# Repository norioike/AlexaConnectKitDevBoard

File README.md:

# AlexaConnectKit Dev-Boardについて
この基板は主にAlexa Connect Kitを使ったデバイスを開発するための開発ボードとして作りました。
RP2040をMCUにAlexaConnectKitのモジュール "ESP32-PICO-V3-ZERO"と通信ができるようになっています。
またRP2040のGPIOは出せるだけ出しているので、センサー類を追加したり駆動系を追加する事でオリジナルのAlexa対応ロボットなどが作れるようになる（と思います)

ただ、この基板単体でも遊べるようにタクトスイッチとフルカラーLEDを実装しています。
しかし、私のミスでフルカラーLEDは点灯しません。電源は5Vにもかかわらず、3.3Vを供給。そのため命令を送っても点灯しません。

部品が余ったので数個だけ頒布しています。
もしよろしければこちらをご覧下さい。

https://www.switch-science.com/catalog/8078/

## Alexa Connect Kitについて
ハードウェアにAlexaを簡単に統合できるようにするためのマネージメントサービスで、これを使うことでAlexaに話しかけるとハードウェアを動かしたり、
逆にセンサー情報をAlexaに送る事ができるハードウェアを簡単に開発する事ができるようになります。
具体的にAlexa内蔵の電子レンジみたいなものを作ることも可能です。

システムの構成は、従来ハードウェアにAlexaと通信ができるモジュールを搭載することで実現できるようになっています。こうすることで開発負荷を下げることを想定しているのだと思います。
今回はESP32-PICO-V3-ZEROがそのモジュールで、この中にAlexaと通信するために必要なファームウェアが書かれており、開発者がこのモジュールとUARTなどで通信できるようにハードウェアを開発すればOKです。
すべての制御は自身が実装したMCUに書くことになります。ここでAlexaに対して命令を送ったり、受け取ったりできるようにすることでAlexa対応のオリジナルデバイスが実現できます。

## セットアップについて
セットアップはWikiにまとめています。このセットアップが完了できれば、あとは自由に開発するだけの状態になります。

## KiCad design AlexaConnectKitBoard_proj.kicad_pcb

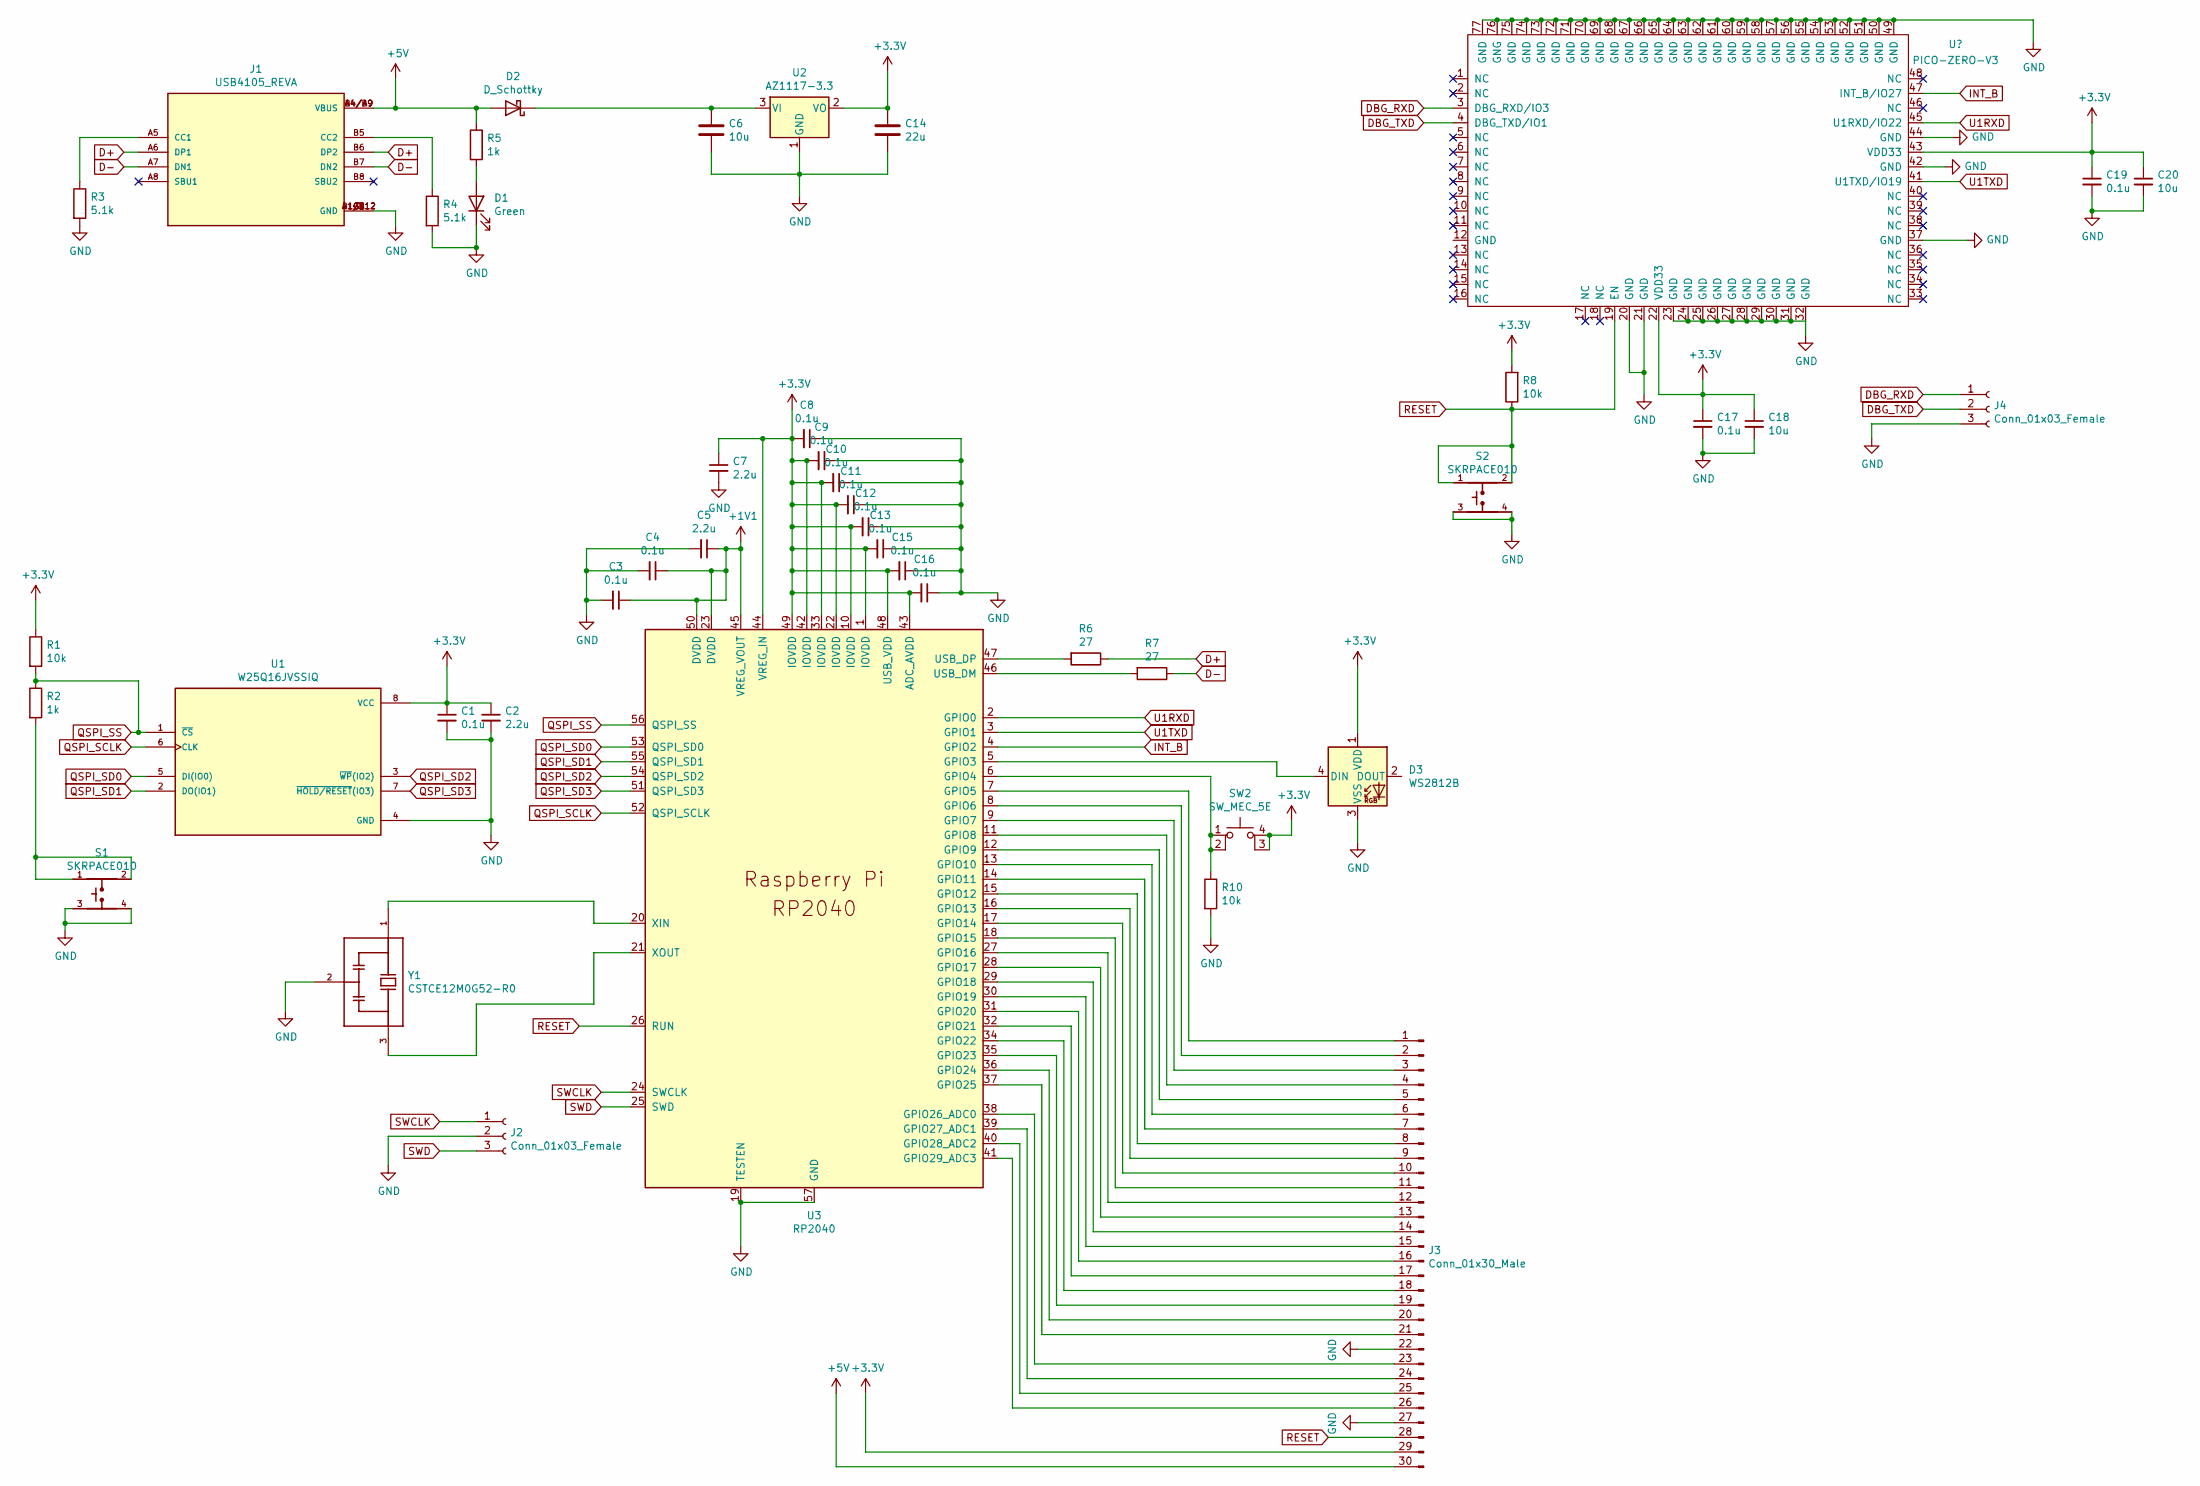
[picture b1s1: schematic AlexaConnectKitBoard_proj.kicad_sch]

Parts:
C1, C3, C4, C8, C9, C10, C11, C12, C13, C15, C16, C17, C19: 0.1u; C_0603_1608Metric
C2, C5, C7: 2.2u; C_0603_1608Metric
C6, C18, C20: 10u; C_0805_2012Metric
C14: 22u; C_0603_1608Metric
D1: Green; LED_0603_1608Metric_Pad1.05x0.95mm_HandSolder
D2: D_Schottky; D_SOD-123F
D3: WS2812B; LED_WS2812B_PLCC4_5.0x5.0mm_P3.2mm
J1: USB4105_REVA; GCT_USB4105_REVA; PARTREV 0.2
J2, J4: Conn_01x03_Female; PinHeader_1x03_P2.54mm_Vertical
J3: Conn_01x30_Male; PinHeader_1x30_P2.54mm_Vertical
R1, R8, R10: 10k; R_0603_1608Metric
R2: 1k; R_0603_1608Metric
R3, R4: 5.1k; R_0603_1608Metric_Pad0.98x0.95mm_HandSolder
R5: 1k; R_0603_1608Metric_Pad0.98x0.95mm_HandSolder
R6, R7: 27; R_0603_1608Metric
S1, S2: SKRPACE010; SW_SKRPACE010
SW2: SW_MEC_5E; SW_SPST_Omron_B3FS-105xP
U1: W25Q16JVSSIQ; SOIC127P790X216-8N
U2: AZ1117-3.3; SOT-223-3_TabPin2
U3: RP2040; RP2040-QFN-56
Y1: CSTCE12M0G52-R0; OSC_CSTCE12M0G52-R0; PARTREV May 7, 2019

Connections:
+1V1: C3.1, C4.1, C5.1, U3.23 (DVDD), U3.45 (VREG_VOUT), U3.50 (DVDD)
+3V3: C1.1, C2.1, C7.1, C8.2, C9.2, C10.2, C11.2, C12.2, C13.2, C14.1, C15.2, C16.2, C17.1, C18.1, C19.1, C20.1, D3.1 (VDD), J3.29, R1.1, R8.2, SW2.3 (K), SW2.4 (A), U1.8 (VCC), U2.2 (VO), U3.1 (IOVDD), U3.10 (IOVDD), U3.22 (IOVDD), U3.33 (IOVDD), U3.42 (IOVDD), U3.43 (ADC_AVDD), U3.44 (VREG_IN), U3.48 (USB_VDD), U3.49 (IOVDD); also elsewhere on the board
+5V: D2.2 (A), J1.A4/B9 (VBUS), J1.B4/A9 (VBUS), J3.30, R5.1
D+: J1.A6 (DP1), J1.B6 (DP2), R6.1
D-: J1.A7 (DN1), J1.B7 (DN2), R7.1
DBG_RXD: J4.1; also elsewhere on the board
DBG_TXD: J4.2; also elsewhere on the board
GND: C1.2, C2.2, C3.2, C4.2, C5.2, C6.2, C7.2, C8.1, C9.1, C10.1, C11.1, C12.1, C13.1, C14.2, C15.1, C16.1, C17.2, C18.2, C19.2, C20.2, D1.1 (K), D3.3 (VSS), J1.A1/B12 (GND), J1.B1/A12 (GND), J1.G1 (GND), J1.G2 (GND), J1.G3 (GND), J1.G4 (GND), J2.2, J3.22, J3.27, J4.3, R3.2, R4.2, R10.2, S1.3, S1.4, S2.3, S2.4, U1.4 (GND), U2.1 (GND), U3.19 (TESTEN), U3.57 (GND), Y1.2; also elsewhere on the board
INT_B: U3.4 (GPIO2); also elsewhere on the board
unnamed: C6.1, D2.1 (K), U2.3 (VI)
unnamed: D1.2 (A), R5.2
unnamed 11: D3.4 (DIN), U3.5 (GPIO3); also elsewhere on the board
unnamed: J1.A5 (CC1), R3.1
unnamed: J1.B5 (CC2), R4.1
unnamed: J3.1, U3.7 (GPIO5)
unnamed: J3.2, U3.8 (GPIO6)
unnamed: J3.3, U3.9 (GPIO7)
unnamed: J3.4, U3.11 (GPIO8)
unnamed: J3.5, U3.12 (GPIO9)
unnamed: J3.6, U3.13 (GPIO10)
unnamed: J3.7, U3.14 (GPIO11)
unnamed: J3.8, U3.15 (GPIO12)
unnamed: J3.9, U3.16 (GPIO13)
unnamed: J3.10, U3.17 (GPIO14)
unnamed: J3.11, U3.18 (GPIO15)
unnamed: J3.12, U3.27 (GPIO16)
unnamed: J3.13, U3.28 (GPIO17)
unnamed: J3.14, U3.29 (GPIO18)
unnamed: J3.15, U3.30 (GPIO19)
unnamed: J3.16, U3.31 (GPIO20)
unnamed: J3.17, U3.32 (GPIO21)
unnamed: J3.18, U3.34 (GPIO22)
unnamed: J3.19, U3.35 (GPIO23)
unnamed: J3.20, U3.36 (GPIO24)
unnamed: J3.21, U3.37 (GPIO25)
unnamed: J3.23, U3.38 (GPIO26_ADC0)
unnamed: J3.24, U3.39 (GPIO27_ADC1)
unnamed: J3.25, U3.40 (GPIO28_ADC2)
unnamed: J3.26, U3.41 (GPIO29_ADC3)
unnamed: R2.2, S1.1, S1.2
unnamed: R6.2, U3.47 (USB_DP)
unnamed: R7.2, U3.46 (USB_DM)
unnamed 42: R10.1, SW2.1, SW2.2, U3.6 (GPIO4); also elsewhere on the board
unnamed: U3.20 (XIN), Y1.1
unnamed: U3.21 (XOUT), Y1.3
QSPI_SCLK: U1.6 (CLK), U3.52 (QSPI_SCLK)
QSPI_SD0: U1.5 (DI(IO0)), U3.53 (QSPI_SD0)
QSPI_SD1: U1.2 (DO(IO1)), U3.55 (QSPI_SD1)
QSPI_SD2: U1.3 (~WP(IO2)), U3.54 (QSPI_SD2)
QSPI_SD3: U1.7 (~HOLD/RESET(IO3)), U3.51 (QSPI_SD3)
QSPI_SS: R1.2, R2.1, U1.1 (~CS), U3.56 (QSPI_SS)
RESET: J3.28, R8.1, S2.1, S2.2, U3.26 (RUN); also elsewhere on the board
SWCLK: J2.1, U3.24 (SWCLK)
SWD: J2.3, U3.25 (SWD)
U1RXD: U3.2 (GPIO0); also elsewhere on the board
U1TXD: U3.3 (GPIO1); also elsewhere on the board

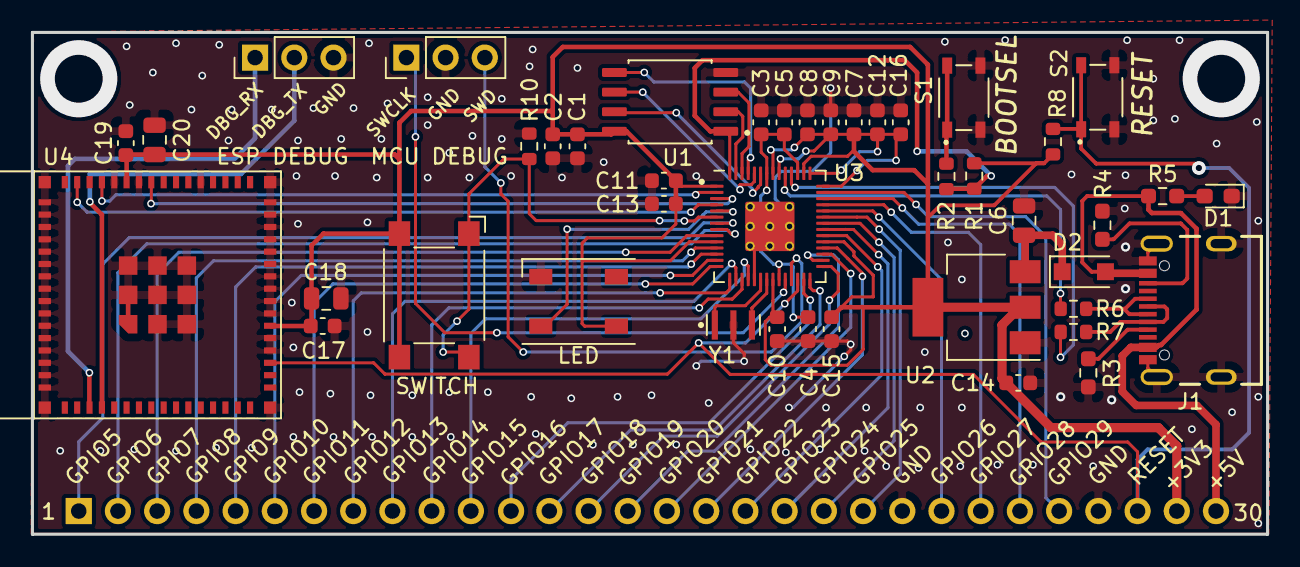
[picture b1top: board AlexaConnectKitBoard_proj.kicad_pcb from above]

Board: 2 copper layers, 80.0 x 32.5 mm, 44 parts (0 on the bottom side), 56 nets.

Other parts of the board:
LED: WS2812B; LED_WS2812B_PLCC4_5.0x5.0mm_P3.2mm
SWITCH: SW_MEC_5E; SW_SPST_Omron_B3FS-105xP
U4: PICO-ZERO-V3; PICO-V3-ZERO

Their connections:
+3V3: LED.1, SWITCH.3, SWITCH.4, U4.22, U4.43; also elsewhere on the board
DBG_RXD: U4.3; also elsewhere on the board
DBG_TXD: U4.4; also elsewhere on the board
GND: LED.3, U4.20, U4.21, U4.23, U4.24, U4.25, U4.26, U4.27, U4.28, U4.29, U4.30, U4.31, U4.32, U4.37, U4.42, U4.44, U4.49, U4.50, U4.51, U4.52, U4.53, U4.54, U4.55, U4.56, U4.57, U4.58, U4.59, U4.60, U4.61, U4.62, U4.63, U4.64, U4.65, U4.66, U4.67, U4.68, U4.69, U4.70, U4.71, U4.72, U4.73, U4.74, U4.75, U4.76, U4.77; also elsewhere on the board
INT_B: U4.47; also elsewhere on the board
unnamed 11: LED.4; also elsewhere on the board
unnamed 42: SWITCH.1, SWITCH.2; also elsewhere on the board
RESET: U4.19; also elsewhere on the board
U1RXD: U4.45; also elsewhere on the board
U1TXD: U4.41; also elsewhere on the board

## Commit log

2022-02-20 upload KiCADデータ
    ACK dev-boardの基板設計データになります
    今回esp32-pico-v3-zeroのライブラリも作りました
